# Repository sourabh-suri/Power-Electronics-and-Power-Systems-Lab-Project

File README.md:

# Power-Electronics-and-Power-Systems-Lab-Project  
Regulated Power Supply Design +15V,-15V and +5V, 1 A current rating.  
DC-DC Buck Converter Design : 30W, 32V to 12V (2% ripple at voltage output).

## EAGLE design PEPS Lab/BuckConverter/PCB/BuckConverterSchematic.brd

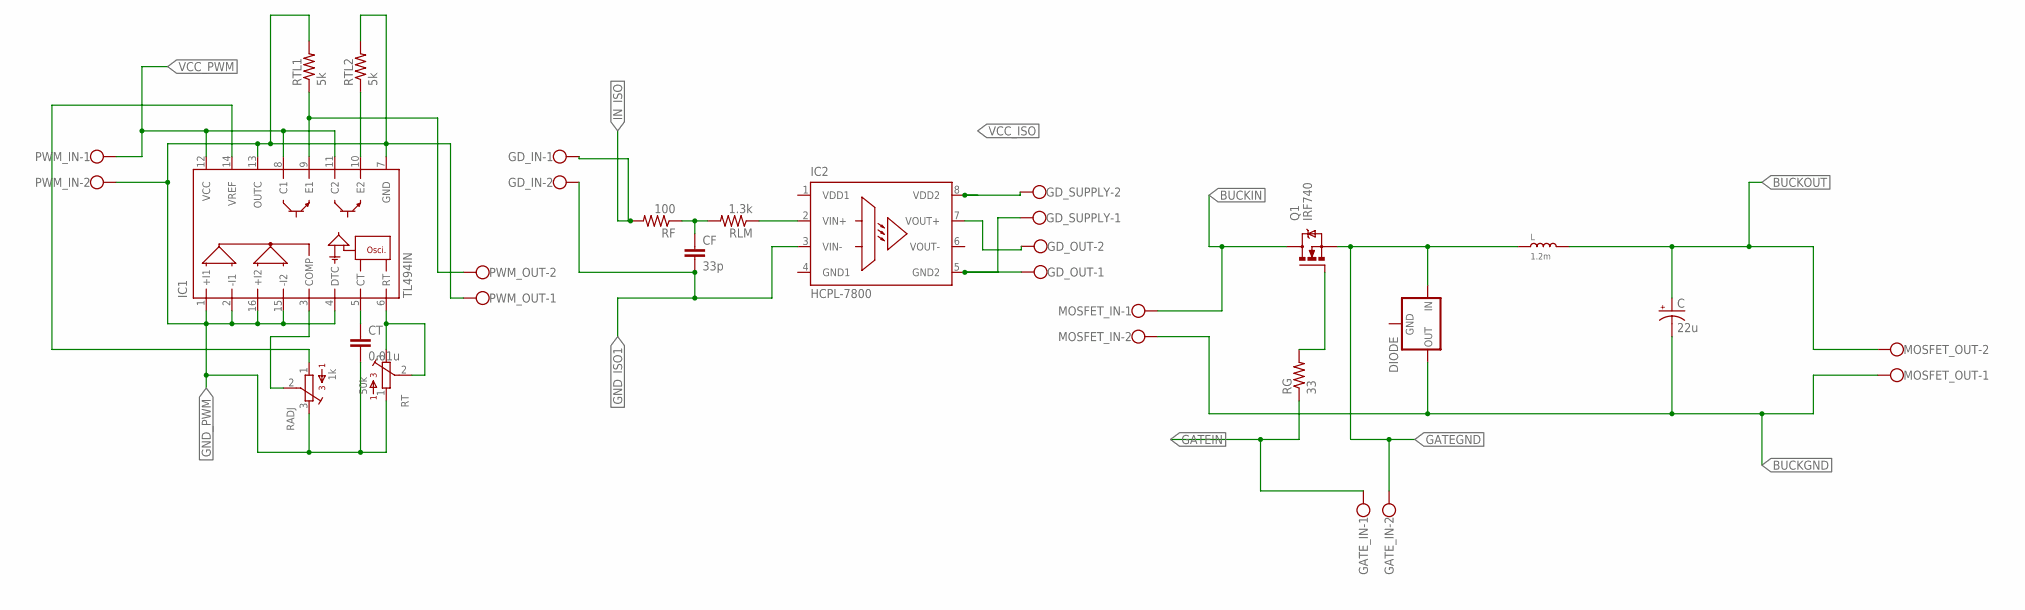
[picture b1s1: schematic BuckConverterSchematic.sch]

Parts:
C: 22u; E2-5
CF: 33p; C025-024X044
CT: 0.01u; C025-024X044
DIODE: 78XXL
GATE_IN: W237-102
GD_IN: W237-102
GD_OUT: W237-102
GD_SUPPLY: W237-102
IC1: TL494IN; DIL16
IC2: HCPL-7800; DIL08
L: 1.2m; FERRITE-CORE-INDUCTOR
MOSFET_IN: W237-102
MOSFET_OUT: W237-102
PWM_IN: W237-102
PWM_OUT: W237-102
Q1: IRF740; TO220BV
RADJ: 1k; 3386P
RF: 100; 0207/9
RG: 33; 0411/15
RLM: 1.3k; 0207/9
RT: 50k; 3386P
RTL1, RTL2: 5k; 0207/9

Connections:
BUCKGND: C.-, DIODE.OUT, MOSFET_IN.2, MOSFET_OUT.1
BUCKIN: MOSFET_IN.1, Q1.D
BUCKOUT: C.+, L.P$2 (L2), MOSFET_OUT.2
GATEGND: DIODE.IN, GATE_IN.2, L.P$1 (L1), Q1.S
GATEIN: GATE_IN.1, RG.1
GND1: IC2.4 (GND1)
GND_ISO1: CF.2, GD_IN.2, IC2.3 (VIN-)
GND_PWM: CT.2, IC1.1 (+I1), IC1.2 (-I1), IC1.4 (DTC), IC1.7 (GND), IC1.13 (OUTC), IC1.15 (-I2), IC1.16 (+I2), PWM_IN.2, PWM_OUT.1, RADJ.3, RT.1, RTL1.2, RTL2.2
IN_ISO: GD_IN.1, RF.2
unnamed: IC1.9 (E1), PWM_OUT.2, RTL1.1
unnamed: IC1.10 (E2), RTL2.1
unnamed: IC1.6 (RT), RT.2, RT.3
unnamed: IC1.3 (COMP), RADJ.2
unnamed: GD_OUT.1, GD_SUPPLY.1, IC2.5 (GND2)
unnamed: CT.1, IC1.5 (CT)
unnamed: GD_OUT.2, IC2.7 (VOUT+)
unnamed: IC1.14 (VREF), RADJ.1
unnamed: Q1.G, RG.2
unnamed: CF.1, RF.1, RLM.2
unnamed: IC2.2 (VIN+), RLM.1
VCC_ISO: GD_SUPPLY.2, IC2.8 (VDD2)
VCC_PWM: IC1.8 (C1), IC1.11 (C2), IC1.12 (VCC), PWM_IN.1
VDD1: IC2.1 (VDD1)
VOUT-: IC2.6 (VOUT-)

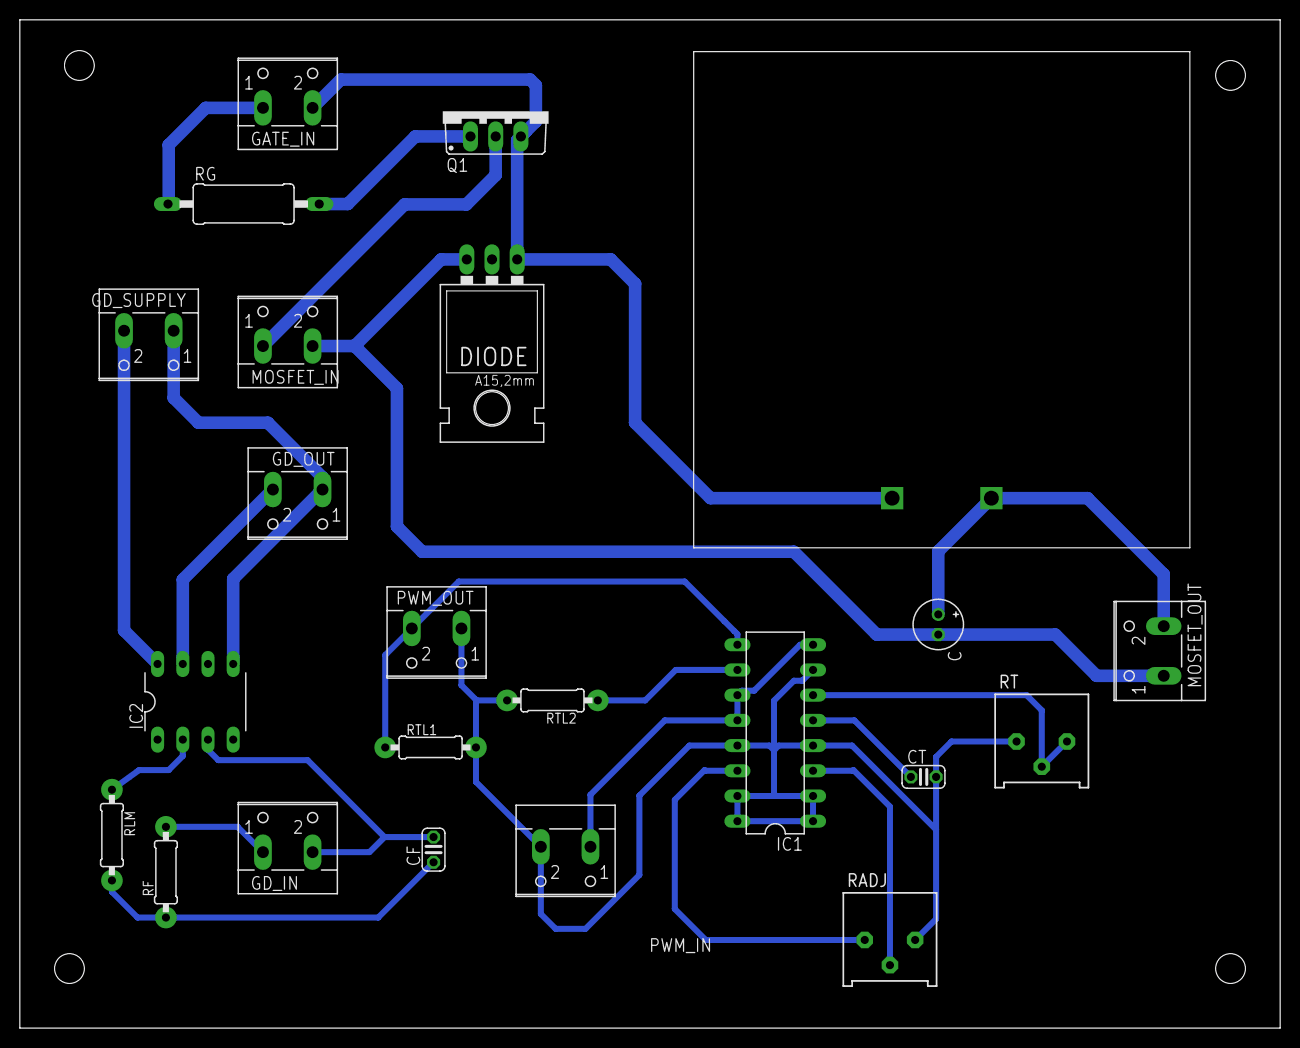
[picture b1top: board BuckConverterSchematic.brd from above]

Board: 2 copper layers, 127.0 x 101.6 mm, 23 parts (0 on the bottom side), 21 nets.
